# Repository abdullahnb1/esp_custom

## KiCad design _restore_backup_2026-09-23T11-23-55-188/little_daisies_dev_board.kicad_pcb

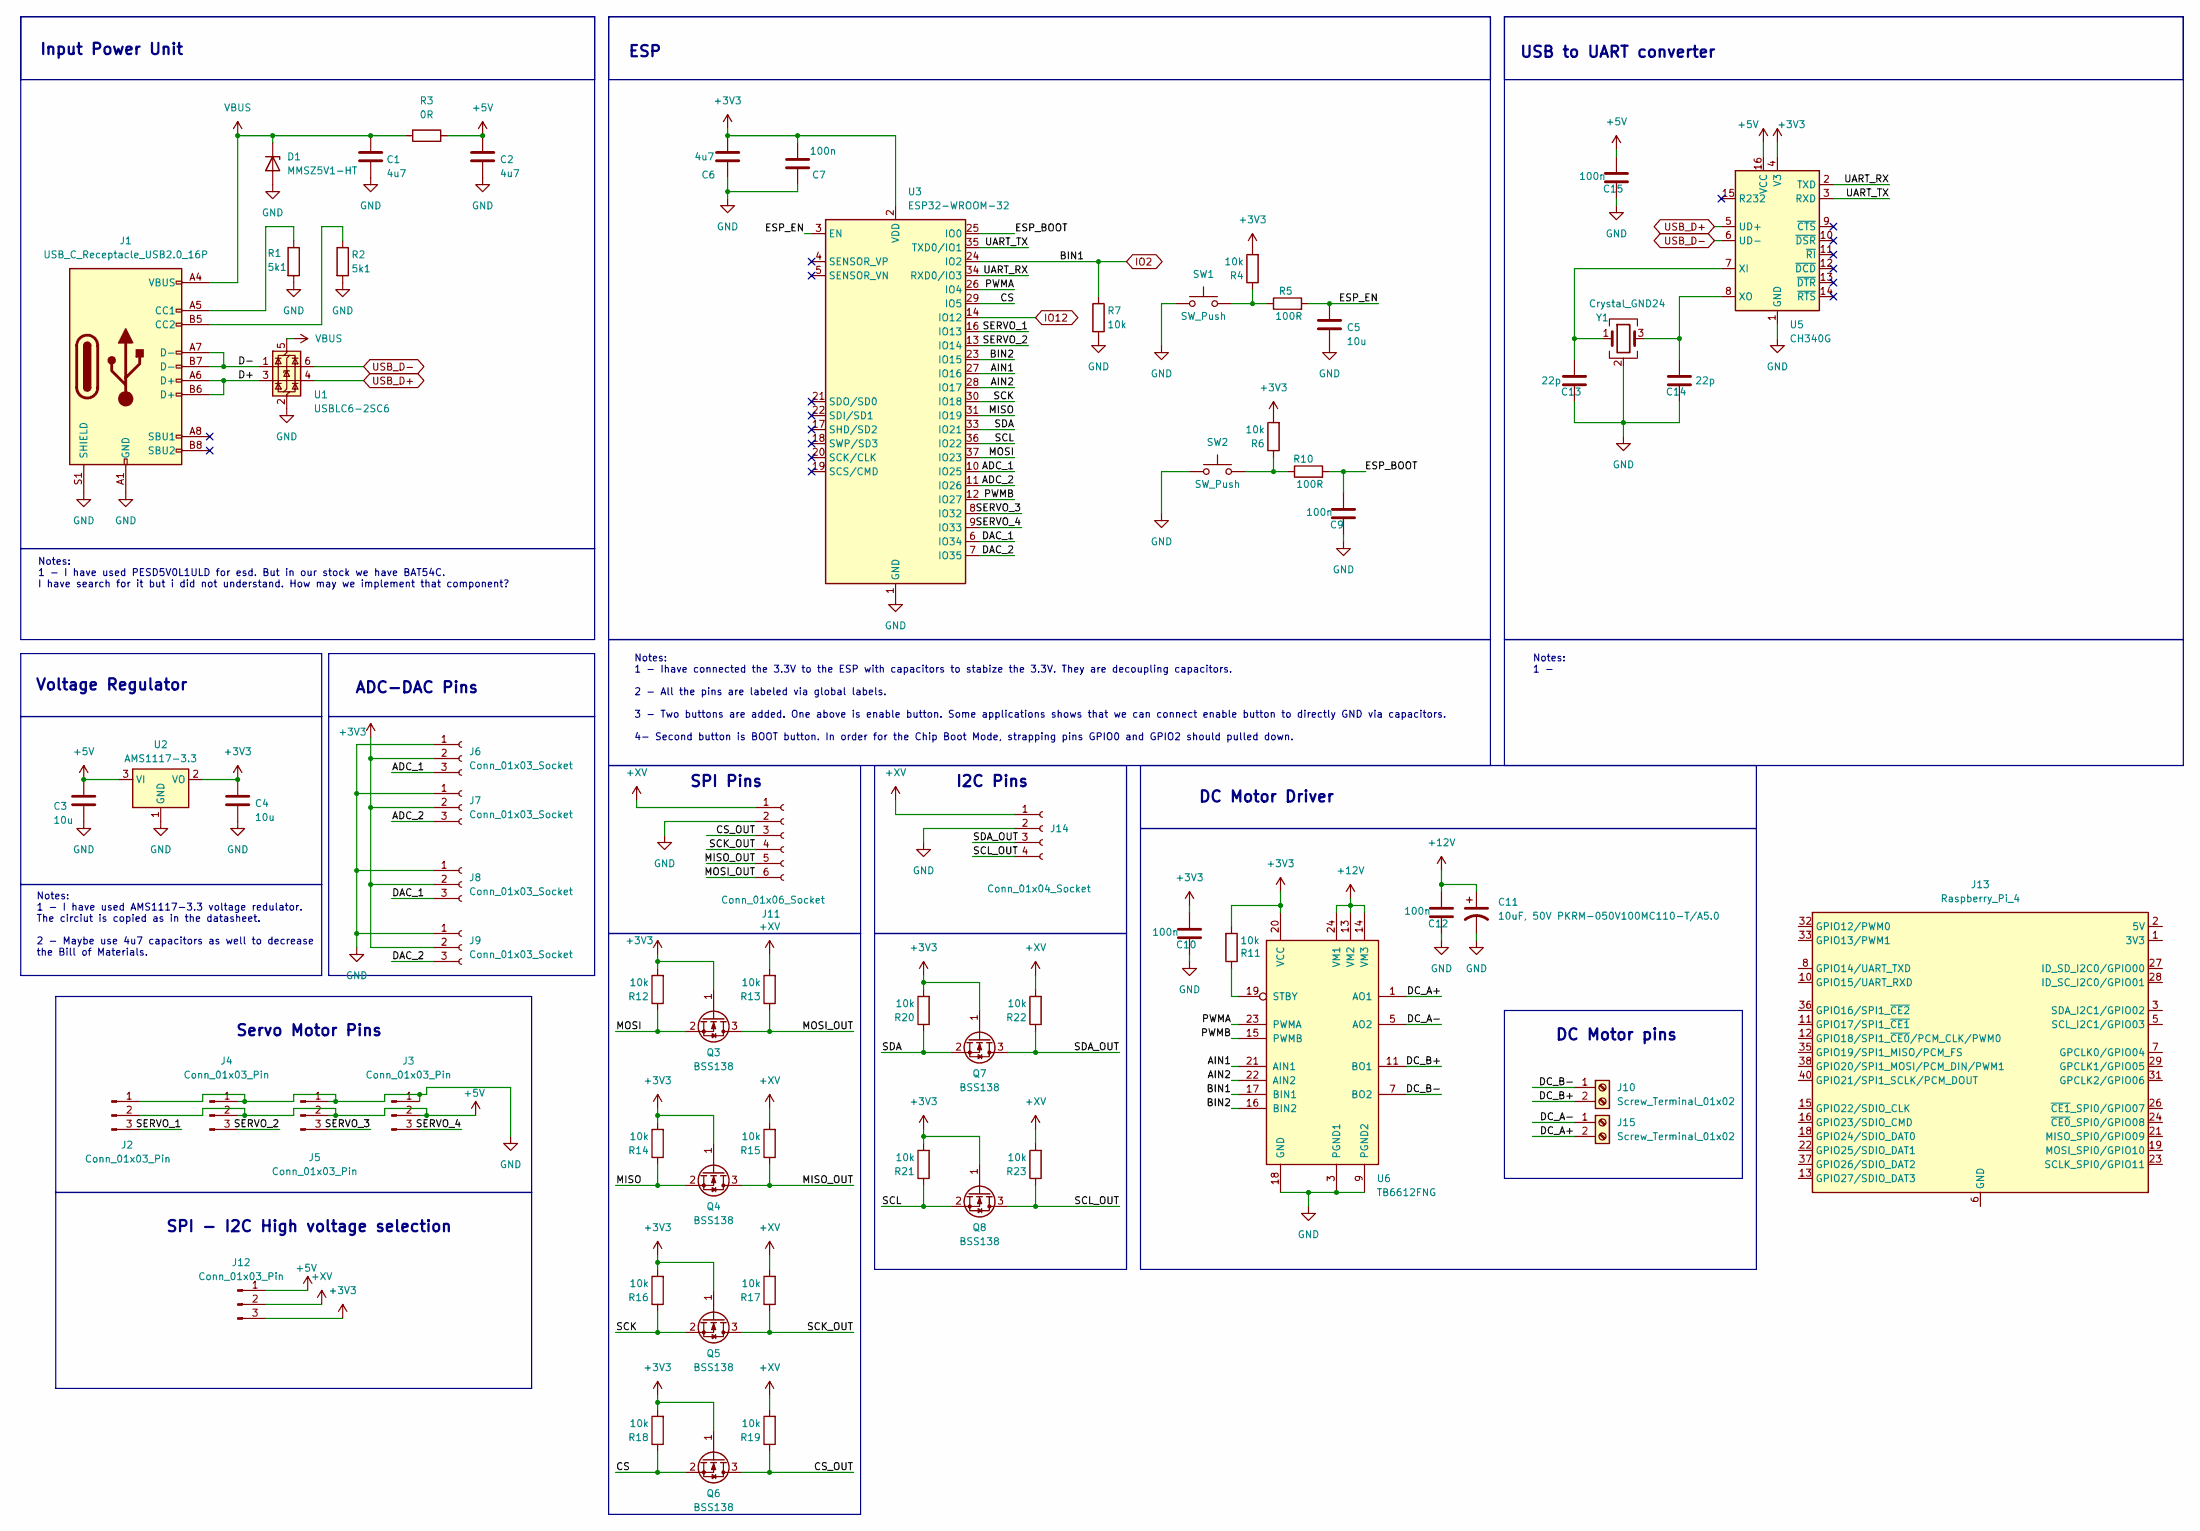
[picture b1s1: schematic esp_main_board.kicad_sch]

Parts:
C1, C2, C6: 4u7; C_0402_1005Metric
C3, C4, C5: 10u; C_0402_1005Metric
C7, C9, C10, C12, C15: 100n; C_0402_1005Metric
C11: 10uF, 50V PKRM-050V100MC110-T/A5.0; C_Radial_D5.0mm_H11.0mm_P2.00mm
C13, C14: 22p; C_0402_1005Metric
D1: MMSZ5V1-HT; SOT-23
J1: USB_C_Receptacle_USB2.0_16P; USB_C_Receptacle_G-Switch_GT-USB-7010ASV
J2, J3, J4, J5, J12: Conn_01x03_Pin; PinHeader_1x03_P2.54mm_Vertical
J6, J7, J8, J9: Conn_01x03_Socket; PinSocket_1x03_P2.54mm_Vertical
J10, J15: Screw_Terminal_01x02; TerminalBlock_Phoenix_MPT-0,5-2-2.54_1x02_P2.54mm_Horizontal
J11: Conn_01x06_Socket; PinSocket_1x06_P2.54mm_Vertical
J13: Raspberry_Pi_4; PinSocket_2x20_P2.54mm_Vertical
J14: Conn_01x04_Socket; PinSocket_1x04_P2.54mm_Vertical
Q3, Q4, Q5, Q6, Q7, Q8: BSS138; SOT-23
R1, R2: 5k1; R_0402_1005Metric
R3: 0R; R_0402_1005Metric
R4, R6, R7, R11, R12, R13, R14, R15, R16, R17, R18, R19, R20, R21, R22, R23: 10k; R_0402_1005Metric
R5, R10: 100R; R_0402_1005Metric
SW1, SW2: SW_Push; SW_SPST_PTS810
U1: USBLC6-2SC6; SOT-23-6
U2: AMS1117-3.3; SOT-223-3_TabPin2
U3: ESP32-WROOM-32; ESP32-WROOM-32E
U5: CH340G; SOIC-16_3.9x9.9mm_P1.27mm
U6: TB6612FNG; SSOP-24_5.3x8.2mm_P0.65mm
Y1: Crystal_GND24; Crystal_SMD_3225-4Pin_3.2x2.5mm

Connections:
+3V3: C4.1, C6.1, C7.1, C10.1, J6.2, J7.2, J8.2, J9.2, J12.3, Q3.1 (G), Q4.1 (G), Q5.1 (G), Q6.1 (G), Q7.1 (G), Q8.1 (G), R4.2, R6.2, R11.2, R12.2, R14.2, R16.2, R18.2, R20.2, R21.2, U2.2 (VO), U3.2 (VDD), U5.4 (V3), U6.20 (VCC)
+5V: C2.1, C3.1, C15.1, J2.2, J3.2, J4.2, J5.2, J12.1, R3.2, U2.3 (VI), U5.16 (VCC)
+12V: C11.1, C12.1, U6.13 (VM2), U6.14 (VM3), U6.24 (VM1)
+XV: J11.1, J12.2, J14.1, R13.2, R15.2, R17.2, R19.2, R22.2, R23.2
/ESP_main_board/ADC_1: J6.3, U3.10 (IO25)
/ESP_main_board/ADC_2: J7.3, U3.11 (IO26)
/ESP_main_board/AIN1: U3.27 (IO16), U6.21 (AIN1)
/ESP_main_board/AIN2: U3.28 (IO17), U6.22 (AIN2)
/ESP_main_board/BIN2: U6.16 (BIN2)
/ESP_main_board/CS: Q6.2 (S), R18.1, U3.29 (IO5)
/ESP_main_board/CS_OUT: J11.3, Q6.3 (D), R19.1
/ESP_main_board/D+: J1.A6 (D+), J1.B6 (D+), U1.3 (I/O2)
/ESP_main_board/D-: J1.A7 (D-), J1.B7 (D-), U1.1 (I/O1)
/ESP_main_board/DAC_1: J8.3, U3.6 (IO34)
/ESP_main_board/DAC_2: J9.3, U3.7 (IO35)
/ESP_main_board/DC_A+: J15.2, U6.1 (AO1), U6.2 (AO1)
/ESP_main_board/DC_A-: J15.1, U6.5 (AO2), U6.6 (AO2)
/ESP_main_board/DC_B+: J10.2, U6.11 (BO1), U6.12 (BO1)
/ESP_main_board/DC_B-: J10.1, U6.7 (BO2), U6.8 (BO2)
/ESP_main_board/ESP_BOOT: C9.1, R10.2, U3.25 (IO0)
/ESP_main_board/ESP_EN: C5.1, R5.2, U3.3 (EN)
/ESP_main_board/MISO: Q4.2 (S), R14.1, U3.31 (IO19)
/ESP_main_board/MISO_OUT: J11.5, Q4.3 (D), R15.1
/ESP_main_board/MOSI: Q3.2 (S), R12.1, U3.37 (IO23)
/ESP_main_board/MOSI_OUT: J11.6, Q3.3 (D), R13.1
/ESP_main_board/PWMA: U3.26 (IO4), U6.23 (PWMA)
/ESP_main_board/PWMB: U3.12 (IO27), U6.15 (PWMB)
/ESP_main_board/SCK: Q5.2 (S), R16.1, U3.30 (IO18)
/ESP_main_board/SCK_OUT: J11.4, Q5.3 (D), R17.1
/ESP_main_board/SCL: Q8.2 (S), R21.1, U3.36 (IO22)
/ESP_main_board/SCL_OUT: J14.4, Q8.3 (D), R23.1
/ESP_main_board/SDA: Q7.2 (S), R20.1, U3.33 (IO21)
/ESP_main_board/SDA_OUT: J14.3, Q7.3 (D), R22.1
/ESP_main_board/SERVO_1: J2.3, U3.16 (IO13)
/ESP_main_board/SERVO_2: J4.3, U3.13 (IO14)
/ESP_main_board/SERVO_3: J5.3, U3.8 (IO32)
/ESP_main_board/SERVO_4: J3.3, U3.9 (IO33)
/ESP_main_board/UART_RX: U3.34 (RXD0/IO3), U5.2 (TXD)
/ESP_main_board/UART_TX: U3.35 (TXD0/IO1), U5.3 (RXD)
GND: C1.2, C2.2, C3.2, C4.2, C5.2, C6.2, C7.2, C9.2, C10.2, C11.2, C12.2, C13.2, C14.2, C15.2, D1.2 (A), J1.A1 (GND), J1.A12 (GND), J1.B1 (GND), J1.B12 (GND), J1.S1 (SHIELD), J2.1, J3.1, J4.1, J5.1, J6.1, J7.1, J8.1, J9.1, J11.2, J14.2, R1.2, R2.2, R7.2, SW1.1, SW2.1, U1.2 (GND), U2.1 (GND), U3.1 (GND), U3.15 (GND), U3.38 (GND), U3.39 (GND), U5.1 (GND), U6.3 (PGND1), U6.4 (PGND1), U6.9 (PGND2), U6.10 (PGND2), U6.18 (GND), Y1.2 (G), Y1.4 (G)
IO2: R7.1, U3.24 (IO2), U6.17 (BIN1)
IO12: U3.14 (IO12)
unnamed: J1.A5 (CC1), R1.1
unnamed: J1.B5 (CC2), R2.1
unnamed: J13.1 (3V3), J13.17 (3V3)
unnamed: J13.2 (5V), J13.4 (5V)
unnamed: J13.6 (GND), J13.9 (GND), J13.14 (GND), J13.20 (GND), J13.25 (GND), J13.30 (GND), J13.34 (GND), J13.39 (GND)
unnamed: R4.1, R5.1, SW1.2
unnamed: R6.1, R10.1, SW2.2
unnamed: C13.1, U5.7 (XI), Y1.1
unnamed: C14.1, U5.8 (XO), Y1.3
unnamed: R11.1, U6.19 (STBY)
USB_D+: U1.4 (I/O2), U5.5 (UD+)
USB_D-: U1.6 (I/O1), U5.6 (UD-)
VBUS: C1.1, D1.1 (K), J1.A4 (VBUS), J1.A9 (VBUS), J1.B4 (VBUS), J1.B9 (VBUS), R3.1, U1.5 (VBUS)

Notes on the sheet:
USB to UART converter
Notes: 1 - I have used AMS1117-3.3 voltage redulator. The circiut is copied as in the datasheet. 2 - Maybe use 4u7 capacitors as well to decrease the Bill of Materials.
Notes: 1 - Ihave connected the 3.3V to the ESP with capacitors to stabize the 3.3V. They are decoupling capacitors. 2 - All the pins are labeled via global labels. 3 - Two buttons are added. One above is enable button. Some applications shows that we can connect enable button to directly GND via ca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
Notes: 1 - I have used PESD5V0L1ULD for esd. But in our stock we have BAT54C. I have search for it but i did not understand. How may we implement that component?
SPI Pins
ESP
SPI - I2C High voltage selection
Input Power Unit
DC Motor pins
Voltage Regulator
Notes: 1 -
DC Motor Driver
ADC-DAC Pins
I2C Pins
Servo Motor Pins

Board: 2 copper layers, 65 parts (0 on the bottom side), 53 nets, no tracks yet.
